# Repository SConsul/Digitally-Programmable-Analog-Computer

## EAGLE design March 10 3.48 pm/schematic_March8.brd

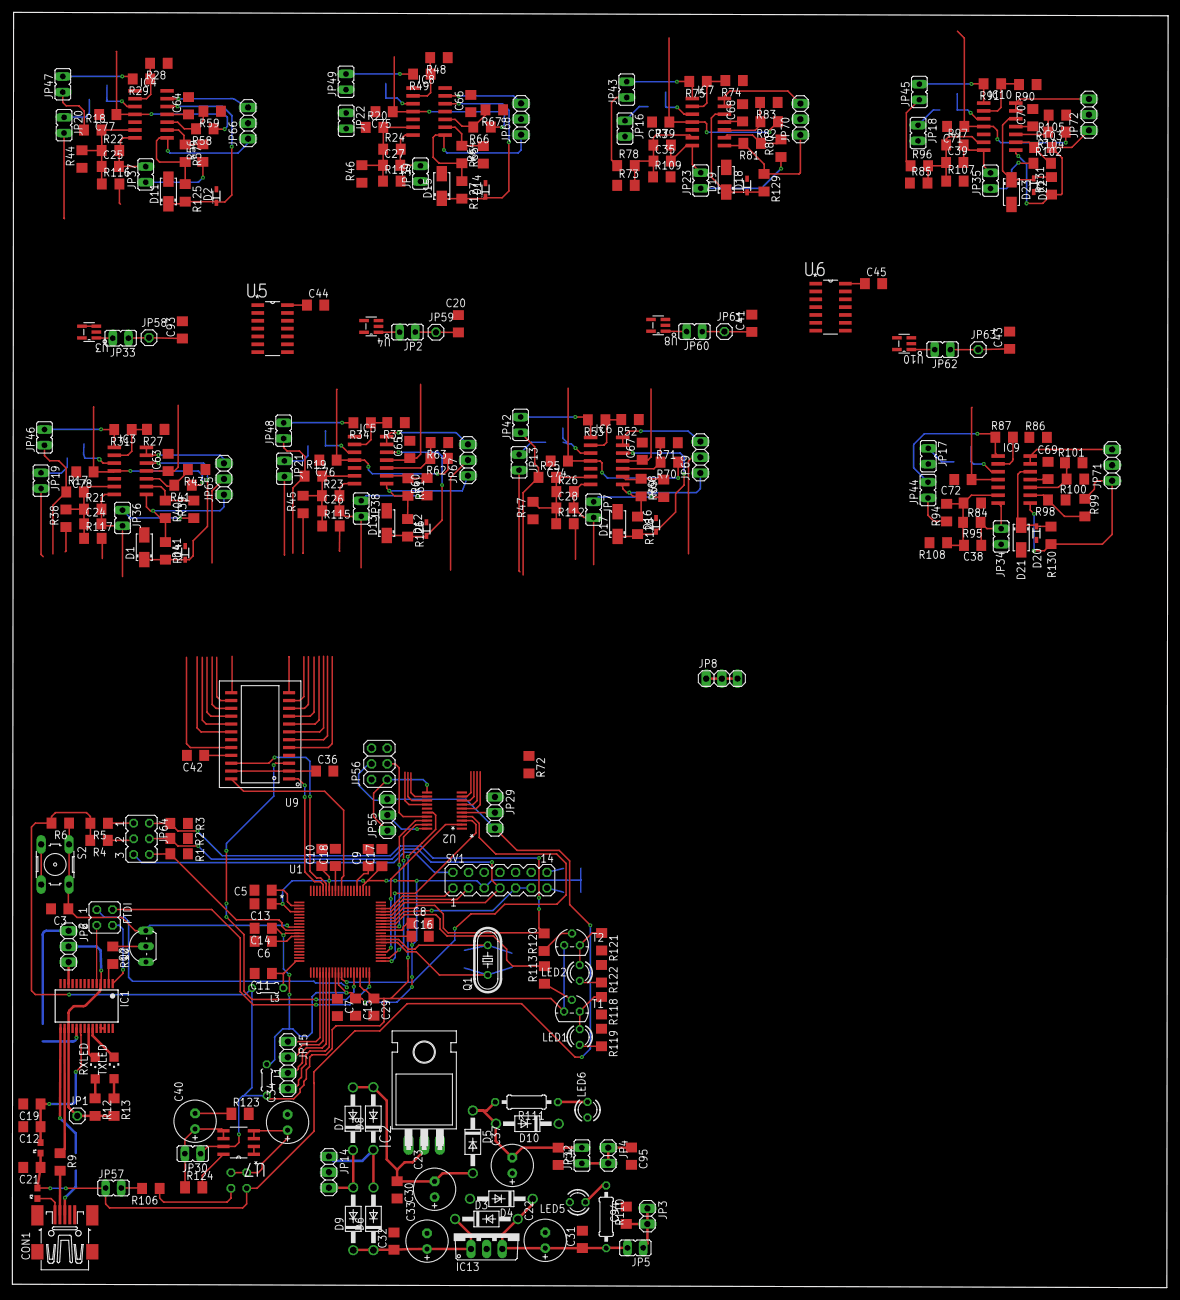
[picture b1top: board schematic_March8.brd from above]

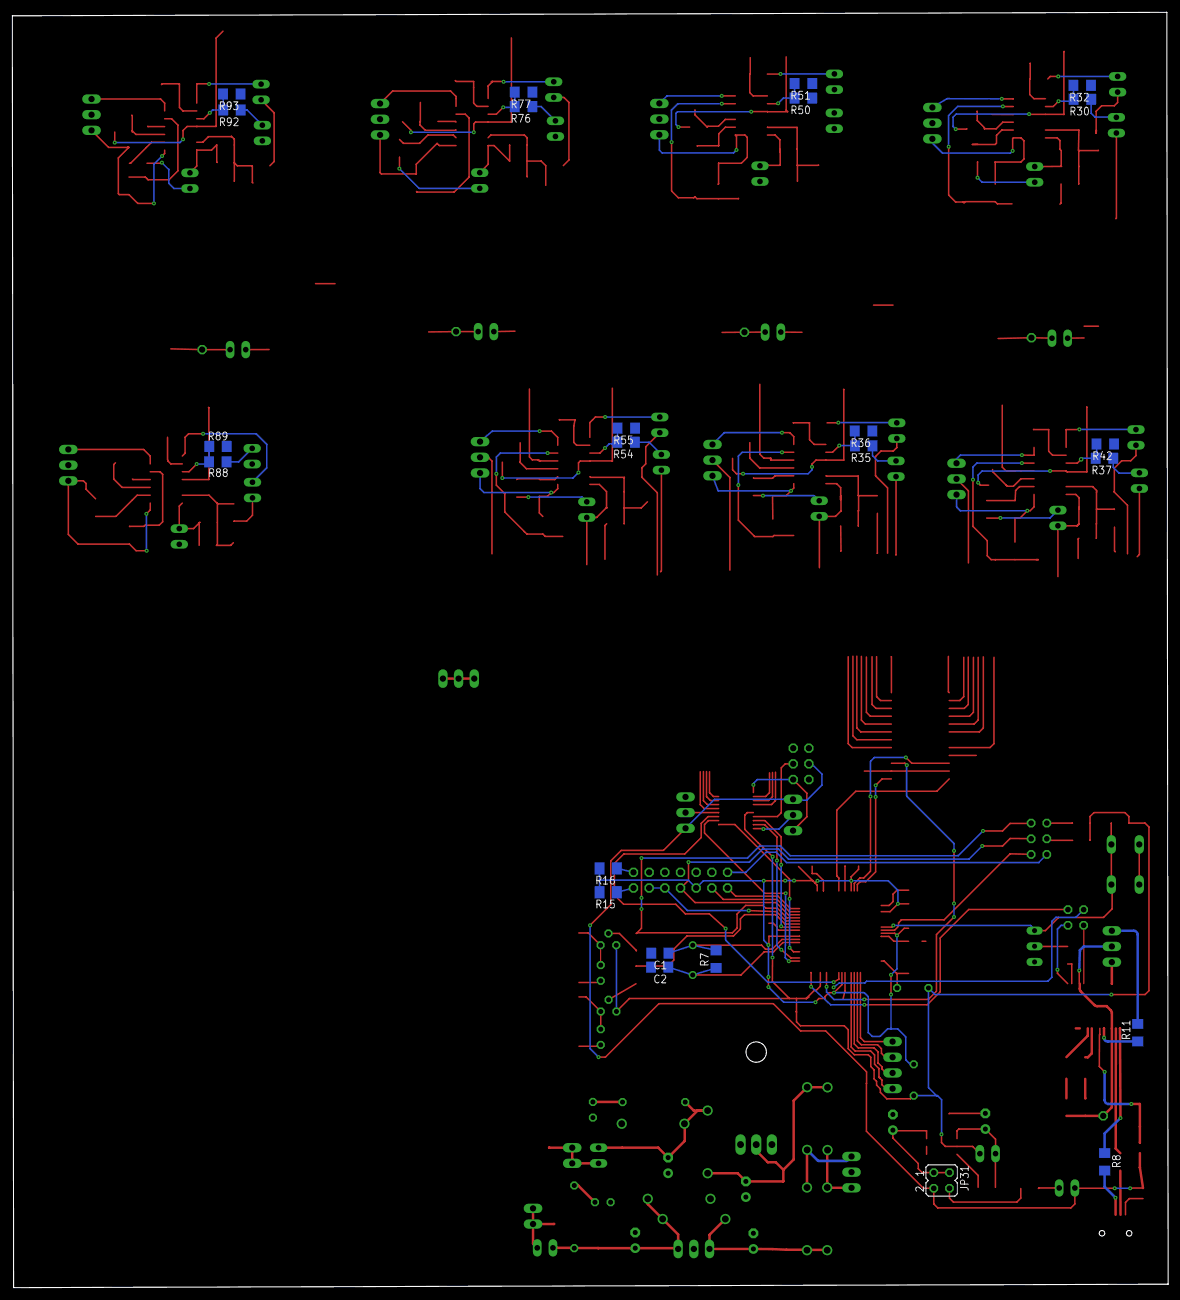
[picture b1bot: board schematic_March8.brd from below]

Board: 2 copper layers, 187.3 x 206.7 mm, 314 parts (24 on the bottom side), 229 nets.

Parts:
C1, C2: 36p; C1206
C3, C29: 0.1u; C1206
C4, C30, C31, C32: 0.1uF; C1206
C5, C6, C7, C8, C9, C10, C11, C13, C14, C15, C16, C17, C18, C20, C36, C41, C42, C43, C44, C45, C63, C64, C65, C66, C67, C68, C69, C70, C71, C72, C73, C74, C75, C76, C77, C78, C93, C94, C95: 2.2u; C1206
C12: 100nF; C1206
C19: 4.7uF; C1206
C21: 10nF; C1206
C22, C37, C40: 10uF; E2,5-7
C23, C33: 1000uF; E2,5-7
C24, C25, C26, C27, C28, C35, C38, C39: C1206
C34: 0.1uF; E2,5-7
CON1: UBC05V128-B0C04D; 32005-201
D1, D11, D13, D15, D17, D19, D21, D23: 1SMA5913BT3G; DO214AC
D2, D12, D14, D16, D18, D20, D22, D41: 1N914BWS; SOD323F
D3, D4, D5, D6, D7, D8, D9, D10: 1N4004; DO41-10
F1, F3: 500mA; 0603
FTDI: JP2Q
IC1: FT232RL; SSOP28
IC2: TO220H
IC3, IC4, IC5, IC6, IC7, IC8, IC9, IC10: TL084D; SO14
IC13: 7805TV; TO220V
JP1, JP58, JP59, JP61, JP63: 1X01
JP2, JP5, JP7, JP13, JP16, JP17, JP18, JP19, JP20, JP21, JP22, JP23, JP30, JP32, JP33, JP35, JP36, JP37, JP38, JP39, JP42, JP43, JP45, JP46, JP47, JP48, JP49, JP57, JP60, JP62: JP1
JP3, JP4: 1X02
JP6, JP8, JP14, JP29, JP55, JP65, JP66, JP67, JP68, JP69, JP70, JP71, JP72: 1X03
JP15: 1X04
JP31: JP2Q
JP34: pls; JP1
JP44: Int_inp; JP1
JP56: 2X03
JP64: JP3Q
L1, L3: BKP1005HS221-T; 0204/5
LED1, LED2, LED5, LED6: LED3MM
Q1: HC49/S
Q2: BC557; TO92-EBC
R1, R2, R3, R6, R10: 2.2k; R1206
R4, R5: 820; R1206
R7: 1M; R1206
R8, R9: 33; R1206
R11, R118, R121: 10k; R1206
R12, R13: 270; R1206
R14, R17, R18, R19, R20, R21, R22, R23, R24, R25, R26, R27, R28, R29, R30, R31, R32, R33, R34, R35, R36, R37, R38, R39, R40, R41, R42, R43, R44, R45, R46, R47, R48, R49, R50, R51, R52, R53, R54, R55, R56, R57, R58, R59, R60, R61, R62, R63, R64, R65, R66, R67, R68, R69, R70, R71, R73, R74, R75, R76, R77, R78, R79, R80, R81, R82, R83, R84, R85, R86, R87, R88, R89, R90, R91, R92, R93, R94, R95, R96, R97, R98, R99, R100, R101, R102, R103, R104, R105, R107, R108, R109, R112, R114, R115, R116, R117, R125, R126, R127, R128, R129, R130, R131: R1206
R15, R16: 4.7k; M1206
R72, R106: 0; R1206
R110, R111: 1K; 0207/10
R113, R119, R120, R122: 470; R1206
R123, R124: 1; M1206
RXLED: CHIPLED_1206
S2: B3F-10XX
SV1: JTAG; MA07-2
T1, T2: BC547; TO92
TXLED: CHIPLED_1206
U1: TMS320F28069_PN_80; PN80
U2: TLV5610_PW_20; PW20
U3, U4, U8, U10: REF2030AIDDCR; DDC0005A_N
U5, U6: TS12A44514DR; SOIC127P600X175-14N
U7: TPS7333QD; SOIC127P600X175-8N
U9: MAX395CWG+; 21-0042B_24

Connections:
3V3_OUT: IC1.4, IC1.17, JP1.1, JP6.2, R12.2, R13.2
+1.5V1: C93.1, JP33.1, JP58.1, R27.1, R28.1
+1.5V2: C20.1, JP2.1, JP59.1, R33.1, R48.1
+1.5V3: C41.1, JP60.1, JP61.1, R52.1, R74.1
+1.5V4: C43.1, JP62.1, JP63.1, R86.1, R90.1
+3V3: C29.1, JP30.1, L1.2, L3.2, R4.2, R5.2, R6.2, T1.3, T2.3, U1.37, U2.16, U7.7
+5V: C36.1, C44.1, C45.1, C71.1, C72.1, C73.1, C74.1, C75.1, C76.1, C77.1, C78.1, C94.1, IC3.4, IC4.4, IC5.4, IC6.4, IC7.4, IC8.4, IC9.4, IC10.4, JP3.1, JP3.2, JP5.1, JP29.1, JP31.4, JP55.1, JP56.1, R41.1, R58.1, R62.1, R66.1, R70.1, R82.1, R100.1, R104.1, R106.1, U2.11, U3.3, U3.4, U4.3, U4.4, U5.14, U6.14, U8.3, U8.4, U9.2, U9.23, U10.3, U10.4
-5V: C42.1, C63.1, C64.1, C65.1, C66.1, C67.1, C68.1, C69.1, C70.1, C95.1, IC3.11, IC4.11, IC5.11, IC6.11, IC7.11, IC8.11, IC9.11, IC10.11, JP4.1, JP4.2, JP32.1, U9.21
?????: JP56.3, U2.17
ADCINA0: JP70.2, U1.19
ADCINA1: JP69.2, U1.18
ADCINA2: JP68.2, U1.17
ADCINA4: JP67.2, U1.16
ADCINA5: JP66.2, U1.15
ADCINA6: JP65.2, U1.14
ADCINB0: JP71.2, U1.22
ADCINB1: JP72.2, U1.23
ADCINB2: JP15.1, U1.24
ADCINB4: JP15.2, U1.25
ADCINB5: JP15.3, U1.26
ADCINB6: JP15.4, U1.27
AGND: C4.2, C20.2, C22.-, C23.+, C30.2, C31.2, C32.2, C33.-, C37.+, C41.2, C43.2, C63.2, C64.2, C65.2, C66.2, C67.2, C68.2, C69.2, C70.2, C71.2, C72.2, C73.2, C74.2, C75.2, C76.2, C77.2, C78.2, C93.2, C94.2, C95.2, D1.A, D2.A, D4.A, D10.C, D11.A, D12.A, D13.A, D14.A, D15.A, D16.A, D17.A, D18.A, D19.A, D20.A, D21.A, D22.A, D23.A, D41.A, IC2.1, IC3.5, IC4.5, IC5.5, IC6.5, IC7.5, IC8.5, IC9.5, IC10.5, IC13.2, JP8.1, JP8.2, JP8.3, LED5.K, LED6.A, R32.1, R36.1, R42.1, R43.1, R51.1, R55.1, R59.1, R63.1, R67.1, R71.1, R72.1, R77.1, R83.1, R89.1, R93.1, R101.1, R105.1, U2.10, U3.2, U4.2, U5.7, U6.7, U8.2, U10.2
BUFIN1: D1.C, D41.C, IC3.12, R14.2
BUFIN2: D2.C, D11.C, IC4.12, R125.2
BUFIN3: D12.C, D13.C, IC5.12, R126.2
BUFIN4: D14.C, D15.C, IC8.12, R127.2
BUFIN5: D16.C, D17.C, IC6.12, R128.2
BUFIN6: D18.C, D19.C, IC7.12, R129.2
BUFIN7: D20.C, D21.C, IC9.12, R130.2
BUFIN8: D22.C, D23.C, IC10.12, R131.2
CBUS4: IC1.12, JP6.3
D+: IC1.15, R8.1
D-: IC1.16, R9.1
DACDIN: U1.44, U2.2
DACDOUT: U1.42, U2.19
DACO1: JP19.2, U2.12
DACO2: JP20.2, U2.13
DACO3: JP21.2, U2.14
DACO4: JP22.2, U2.15
DACO5: JP13.2, U2.6
DACO6: JP16.2, U2.7
DACO7: JP17.2, U2.8
DACO8: JP18.2, U2.9
DTR_RESET: Q2.B, R10.1
FS: U1.31, U2.4
GND: C1.2, C2.2, C3.2, C5.2, C6.2, C7.2, C8.2, C9.2, C10.2, C11.2, C12.2, C13.2, C14.2, C15.2, C16.2, C17.2, C18.2, C19.2, C21.2, C29.2, C34.-, C36.2, C42.2, C44.2, C45.2, CON1.5, IC1.7, IC1.18, IC1.21, IC1.25, IC1.26, JP56.5, Q2.C, R1.1, R2.1, R3.1, R72.2, R118.2, R119.1, R121.2, R122.1, R123.2, S2.3, S2.4, SV1.4, SV1.8, SV1.10, SV1.12, U1.3, U1.13, U1.21, U1.28, U1.38, U1.50, U1.64, U1.71, U1.73, U2.1, U7.1, U7.2, U9.4
GPIO34: JP64.2, R3.2, R120.2, U1.55
IDK: C22.+, C31.1, D3.A, D4.C, IC13.3, JP5.2, R110.2
IDK2: C4.1, C37.-, D5.C, D10.A, IC2.3, JP32.2, R111.2
IN1: JP19.1, R37.1
IN2: JP20.1, R30.1
IN3: JP21.1, R35.1
IN4: JP22.1, R50.1
IN5: JP13.1, R54.1
IN6: JP16.1, R76.1
IN7: JP17.1, R88.1
IN8: JP18.1, R92.1
INTINP1: JP46.1, R17.1, U9.5
INTINP2: JP47.1, R18.1, U9.7
INTINP3: JP48.1, R19.1, U9.9
INTINP4: JP49.1, R20.1, U9.11
INTINP5: JP42.1, R25.1, U9.14
INTINP6: JP43.1, R78.1, U9.16
INTINP7: JP44.1, R94.1, U9.18
INTINP8: JP45.1, R96.1, U9.20
INTSWITCH1: R117.2, U5.2
INTSWITCH2: R116.2, U5.4
INTSWITCH3: R115.2, U5.9
INTSWITCH4: R114.2, U5.10
INTSWITCH5: R112.2, U6.2
INTSWITCH6: R109.2, U6.4
INTSWITCH7: R108.2, U6.9
INTSWITCH8: R107.2, U6.10
INT_CONTROL: U1.43, U5.5, U5.6, U5.12, U5.13, U6.5, U6.6, U6.12, U6.13
JTAG_TRST: JP64.5, SV1.2
LDACBAR: U1.52, U2.18
LED1: R113.2, U1.53
LIMO1: IC3.13, IC3.14, JP65.3
LIMO2: IC4.13, IC4.14, JP66.3
LIMO3: IC5.13, IC5.14, JP67.3
LIMO4: IC8.13, IC8.14, JP68.3
LIMO5: IC6.13, IC6.14, JP69.3
LIMO6: IC7.13, IC7.14, JP70.3
LIMO7: IC9.13, IC9.14, JP71.3
LIMO8: IC10.13, IC10.14, JP72.3
unnamed: C5.1, U1.2
unnamed: C6.1, U1.12
unnamed: C7.1, U1.29
unnamed: C8.1, U1.51
unnamed: C9.1, U1.65
unnamed: IC1.2, R10.2
unnamed: C11.1, L3.1, U1.20
unnamed: C18.1, U1.72
unnamed: JP64.1, R5.1
unnamed: JP64.3, R4.1
unnamed: CON1.2, R9.2
unnamed: CON1.3, R8.2
unnamed: IC1.19, R11.1
unnamed: IC1.22, RXLED.C
unnamed: IC1.23, TXLED.C
unnamed: R12.1, RXLED.A
unnamed: R13.1, TXLED.A
unnamed: C25.1, IC4.6, R18.2, R22.1, R44.2, R116.1
unnamed: C26.1, IC5.6, R19.2, R23.1, R45.2, R115.1
unnamed: C27.1, IC8.6, R20.2, R24.1, R46.2, R114.1
unnamed: IC4.2, R28.2, R29.1
unnamed: R15.1, SV1.13
unnamed: R16.1, SV1.14
unnamed: IC4.3, R30.2, R32.2
unnamed: C24.1, IC3.6, R17.2, R21.1, R38.2, R117.1
unnamed: IC3.2, R27.2, R31.1
unnamed: C28.1, IC6.6, R25.2, R26.1, R47.2, R112.1
unnamed: IC5.2, R33.2, R34.1
unnamed: IC3.3, R37.2, R42.2
unnamed: IC5.3, R35.2, R36.2
unnamed: IC3.9, R39.2, R40.1
unnamed: IC3.10, R41.2, R43.2
unnamed: IC8.2, R48.2, R49.1
unnamed: IC8.3, R50.2, R51.2
unnamed: IC7.2, R74.2, R75.1
unnamed: IC6.2, R52.2, R53.1
unnamed: IC6.3, R54.2, R55.2
unnamed: IC7.3, R76.2, R77.2
unnamed: IC4.9, R56.2, R57.1
unnamed: IC4.10, R58.2, R59.2
unnamed: IC5.9, R60.2, R61.1
unnamed: IC5.10, R62.2, R63.2
unnamed: IC8.9, R64.2, R65.1
unnamed: IC8.10, R66.2, R67.2
unnamed: IC6.9, R68.2, R69.1
unnamed: IC6.10, R70.2, R71.2
unnamed: C35.1, IC7.6, R73.2, R78.2, R79.1, R109.1
unnamed: IC7.9, R80.2, R81.1
unnamed: IC7.10, R82.2, R83.2
unnamed: IC9.2, R86.2, R87.1
unnamed: IC9.3, R88.2, R89.2
unnamed: IC10.2, R90.2, R91.1
unnamed: IC10.3, R92.2, R93.2
unnamed: C38.1, IC9.6, R84.2, R94.2, R95.1, R108.1
unnamed: C39.1, IC10.6, R85.2, R96.2, R97.1, R107.1
unnamed: IC9.9, R98.2, R99.1
unnamed: IC9.10, R100.2, R101.2
unnamed: IC10.9, R102.2, R103.1
unnamed: IC10.10, R104.2, R105.2
unnamed: C32.1, C33.+, D3.C, D6.C, D9.C, IC13.1
unnamed: C40.+, JP30.2, R124.1, U7.5, U7.6
unnamed: C40.-, R123.1
unnamed: LED6.K, R111.1
unnamed: C34.+, JP31.1, JP31.3, U7.3, U7.4
unnamed: LED5.A, R110.1
unnamed: CON1.1, F3.1
unnamed: C23.-, C30.1, D5.A, D7.A, D8.A, IC2.2
unnamed: JP33.2, U3.1
unnamed: JP6.1, R11.2
unnamed: R113.1, T1.2
unnamed: LED1.A, R118.1, T1.1
unnamed: LED1.K, R119.2
unnamed: R120.1, T2.2
unnamed: LED2.A, R121.1, T2.1
unnamed: LED2.K, R122.2
unnamed: JP55.2, U2.20
unnamed: JP2.2, U4.1
unnamed: JP29.2, U2.5
unnamed: JP57.2, R106.2
unnamed: JP60.2, U8.1
unnamed: JP62.2, U10.1
OUT1: IC3.8, JP65.1, R14.1, R40.2
OUT2: IC4.8, JP66.1, R57.2, R125.1
OUT3: IC5.8, JP67.1, R61.2, R126.1
OUT4: IC8.8, JP68.1, R65.2, R127.1
OUT5: IC6.8, JP69.1, R69.2, R128.1
OUT6: IC7.8, JP70.1, R81.2, R129.1
OUT7: IC9.8, JP71.1, R99.2, R130.1
OUT8: IC10.8, JP72.1, R103.2, R131.1
PLS1: JP36.1, R39.1
PLS2: JP37.1, R56.1
PLS3: JP38.1, R60.1
PLS4: JP39.1, R64.1
PLS5: JP7.1, R68.1
PLS6: JP23.1, R80.1
PLS7: JP34.1, R98.1
PLS8: JP35.1, R102.1
RES: R124.2, U7.8
RESET#: C3.1, Q2.E, R6.1, S2.1, S2.2, U1.9
RXD: FTDI.2, IC1.5
SPIBCLK: U1.76, U9.1
SPIBMISO: U1.75, U9.22
SPIBMOSI: U1.35, U9.3
SPIBSS: U1.70, U9.24
SPICLK: U1.41, U2.3
SV1-1: D7.C, D9.A, JP14.3
SV1-3: D6.A, D8.C, JP14.1
SWITCH1: R38.1, U9.6
SWITCH2: R44.1, U9.8
SWITCH3: R45.1, U9.10
SWITCH4: R46.1, U9.12
SWITCH5: R47.1, U9.13
SWITCH6: R73.1, U9.15
SWITCH7: R84.1, U9.17
SWITCH8: R85.1, U9.19
TCK: SV1.9, SV1.11, U1.54
TDI: SV1.3, U1.57
TDO: JP64.4, R2.2, SV1.7, U1.56
TMS: SV1.1, U1.58
TMS_RXD: FTDI.3, U1.40
TMS_TXD: FTDI.1, U1.34
TRST: JP64.6, R1.2, U1.10
TXD: FTDI.4, IC1.1
USB_VCC: C21.1, F1.1, F3.2, JP29.3, JP31.2, JP55.3, JP56.4, JP57.1
VCC: C12.1, C19.1, F1.2, IC1.20
VDDIO: C10.1, C13.1, C14.1, C15.1, C16.1, C17.1, L1.1, R15.2, R16.2, SV1.5, U1.4, U1.11, U1.30, U1.49, U1.63, U1.74
X1: C24.2, IC3.7, JP36.2, R21.2, U5.1
X1CLK: C1.1, Q1.2, R7.2, U1.48
X1DOT: IC3.1, JP46.2, R31.2
X2: C25.2, IC4.7, JP37.2, R22.2, U5.3
X2CLK: C2.1, Q1.1, R7.1, U1.47
X2DOT: IC4.1, JP47.2, R29.2
X3: C26.2, IC5.7, JP38.2, R23.2, U5.8
X3DOT: IC5.1, JP48.2, R34.2
X4: C27.2, IC8.7, JP39.2, R24.2, U5.11
X4DOT: IC8.1, JP49.2, R49.2
X5: C28.2, IC6.7, JP7.2, R26.2, U6.1
X5DOT: IC6.1, JP42.2, R53.2
X6: C35.2, IC7.7, JP23.2, R79.2, U6.3
X6DOT: IC7.1, JP43.2, R75.2
X7: C38.2, IC9.7, JP34.2, R95.2, U6.8
X7DOT: IC9.1, JP44.2, R87.2
X8: C39.2, IC10.7, JP35.2, R97.2, U6.11
X8DOT: IC10.1, JP45.2, R91.2
